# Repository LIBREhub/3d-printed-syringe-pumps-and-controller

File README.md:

# 3D printable syringe pumps and controller  

This project is a free and open-source design of versatile lab equipment - syringe pumps and a dual controller, here detailed for microfluidic droplet generation - a modification from this [Open-Source Syringe Pump design](https://doi.org/10.1134/S1061934820030156).

Find about more about this platform and other open-source hardware for bioimaging on the [LIBRE hub website](https://librehub.github.io/). Follow us! [#twitter](https://twitter.com/WenzelLab) [#YouTube](https://www.youtube.com/@librehub) [#LinkedIn](https://www.linkedin.com/company/92802424) [#instagram](https://www.instagram.com/wenzellab/) [#Printables](https://www.printables.com/@WenzelLab), [IIBM website](https://ingenieriabiologicaymedica.uc.cl/en/people/faculty/821-tobias-wenzel)

## Background

A syringe pump is a device that delivers precise and accurate amounts of fluid over a broad range of flow rates. These devices are versatile and can be used across various fields like healthcare, research, and development, playing a crucial role in scenarios such as controlled drug delivery in hospitals, chemical reaction control in labs, and more.

There are many 3D-printable syringe pump designs available, each with its unique features and capabilities. However, this [Open-Source Syringe Pump design](https://doi.org/10.1134/S1061934820030156) developed by the [Mass Spectrometry Research Group](https://www.mass-spec.ru/projects/diy/syringe_pump/eng/), Analytical Chemistry Division, Chemistry Department of Moscow State University, appealed to our LIBRE Hub team with its design and functionality.

Our goal with this modification and enhancement is to make this open-source syringe pump design more useful to microfluidics and generally more accessible, adaptable, and user-friendly, thus extending its potential use within the broader community.

## Usage

### Instructions
This Repository provides documentation on how to build the pumps and the controller. Just [follow the instructions here](https://wenzel-lab.github.io/syringe-pumps-and-controller/)

This project is documented with GitBuilding - an Open Source project for documenting hardware projects. For more information on the GitBuilding project or how
to install GitBuilding, please see the [GitBuilding website](http://gitbuilding.io)

## Design files and source code

* Hardware design
    * [Link to OnShape CAD files of printable syringe pump parts](https://cad.onshape.com/documents/20c077b452e92115525d4fed/w/71118f46b0924c1bb22b1150/e/9d30ca00efa721d242d78d3f?renderMode=0&uiState=64bd5f2a8bef574246b008b9)
    * [Link to OnShape CAD files of the printable controller enclosure](https://cad.onshape.com/documents/24a5022fafc4edd0c24874dd/w/35c6569cda7c2fa4439727d4/e/9dbcdcaba091e21e6a91c62c?renderMode=0&uiState=64bd5f3f0aa451311c1bb6ad)
* Software source code
    * [Code to upload onto the Raspberry Pi Pico controller](https://github.com/wenzel-lab/syringe-pumps-and-controller/blob/docu-v1/software/firmwareV1.ino)

### How do I edit the documentation?

To edit the documentation, you do not need to install anything, but you will need to
install something to build the final version of the documentation (such as a website).
The documentation files can be opened in a plain text editor such as Windows Notepad,
Notepad++, gedit, VS Code, etc. GitBuilding also comes with a browser-based editor that
displays a live display of the final HTML documentation.

If you have ever used [markdown](https://www.markdownguide.org/basic-syntax/), you will
notice that the files you are editing are markdown files. GitBuilding uses an extended
markdown syntax (that we call BuildUp). This allows you to keep track of parts in the
documentation. More detail on the documentation is available on the
[GitBuilding website](https://gitbuilding.io/syntax/). There is also additional
[syntax for configuration](https://gitbuilding.io/syntax/buildconfsyntax) and for
[part libraries](https://gitbuilding.io/syntax/builduplibrary/).

## Contribute

Enjoy building and using your improved Open-Source Syringe Pump! We look forward to hearing about your experiences and any further improvements you might have. Make a pull request or [open an issue](https://github.com/wenzel-lab/syringe-pumps-and-controller/issues/new).
For interactions in our team and with the community, apply the [GOSH Code of Conduct](https://openhardware.science/gosh-2017/gosh-code-of-conduct/).

## License

[GNU General Public License v3.0](LICENSE) by Tomás Astudillo, Matías Hurtado, Pierre Padilla-Huamantinco, Tobias Wenzel, and the [original design team](https://www.mass-spec.ru/projects/diy/syringe_pump/eng/). This project is Open Source Hardware - please acknowledge us when using the hardware or sharing modifications.

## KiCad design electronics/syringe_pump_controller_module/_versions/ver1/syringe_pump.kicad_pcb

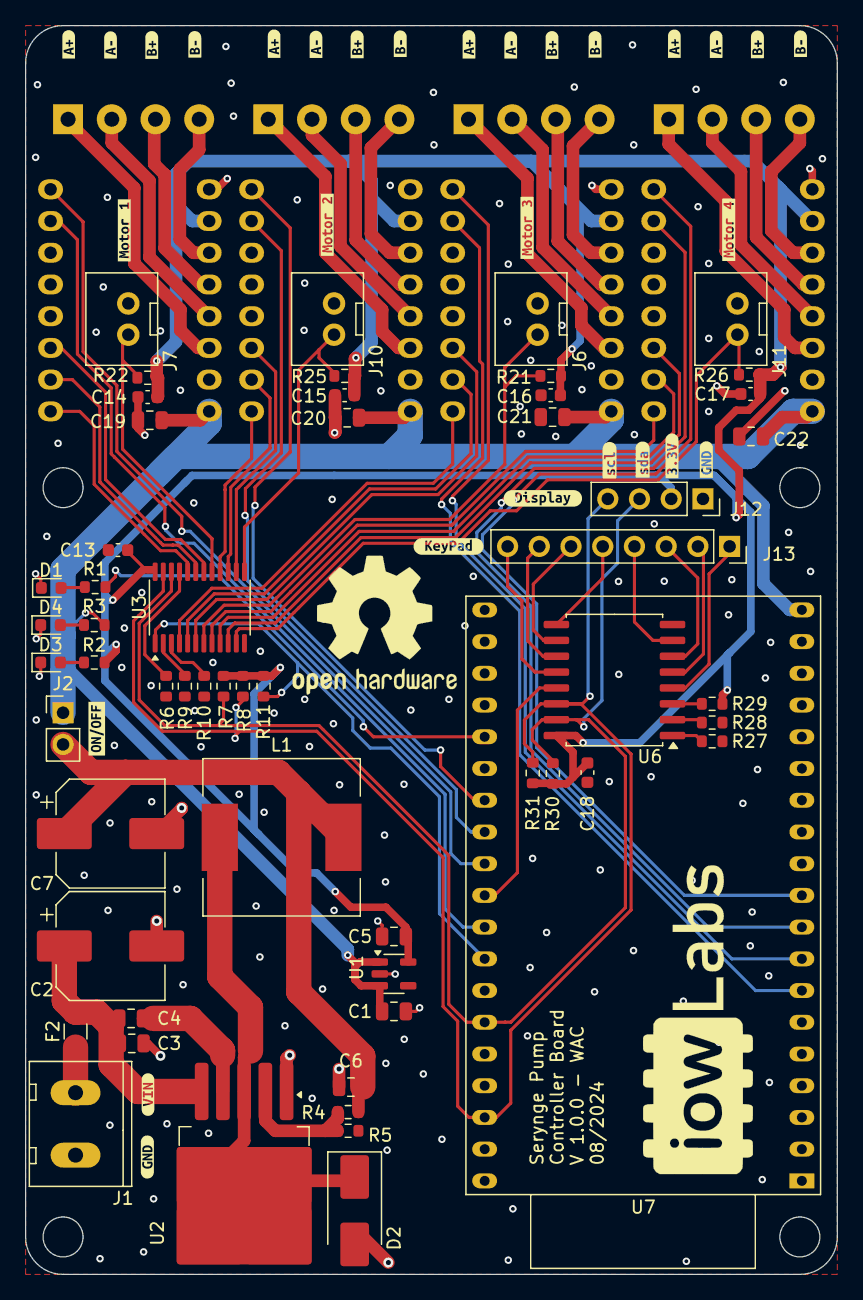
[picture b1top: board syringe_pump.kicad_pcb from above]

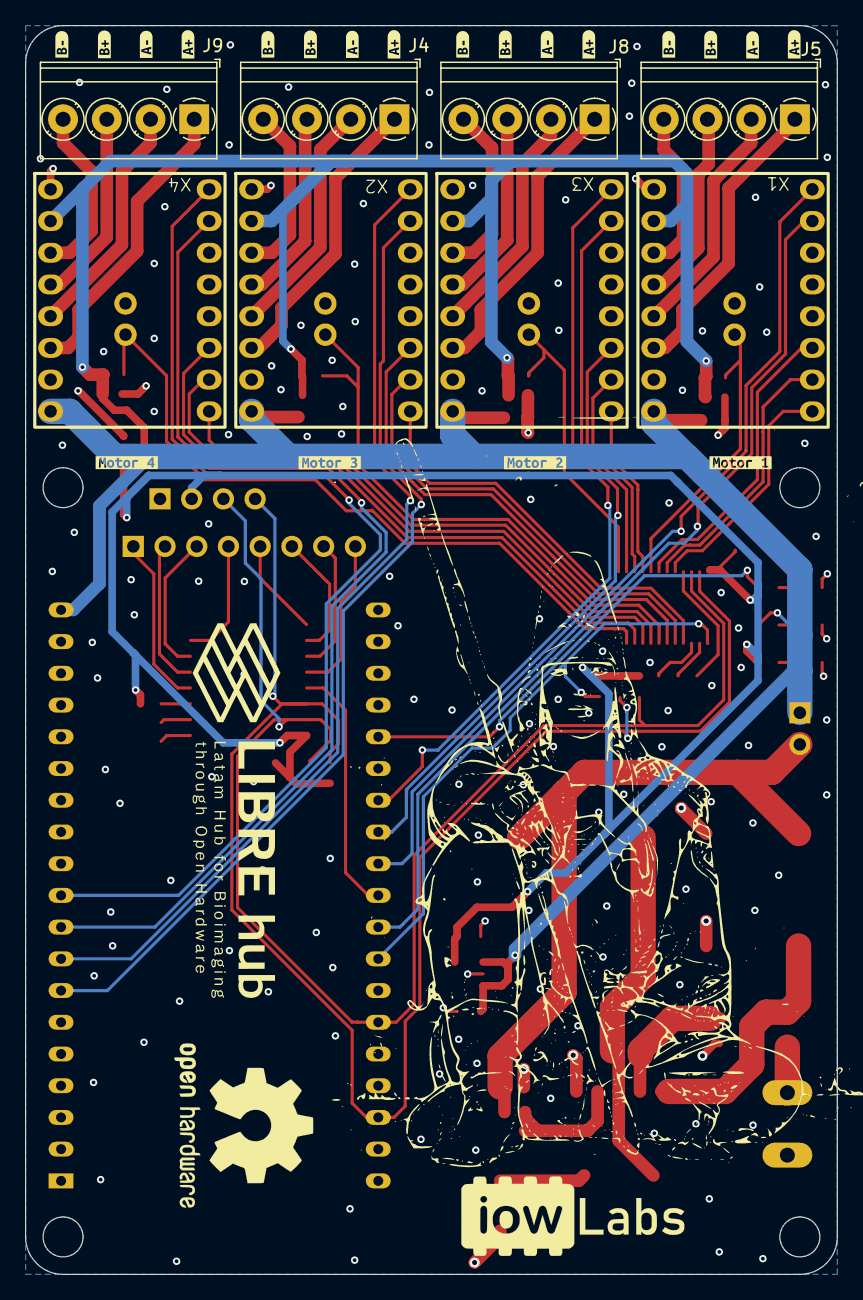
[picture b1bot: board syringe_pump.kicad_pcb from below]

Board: 2 copper layers, 65.0 x 100.0 mm, 113 parts (28 on the bottom side), 71 nets.

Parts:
C1, C3, C4, C5, C6, C19, C20, C21, C22: 1u; C_0805_2012Metric
C2: 220uF; CP_Elec_8x10.5
C7: 330uF; CP_Elec_8x10.5
C13, C14, C15, C16, C17, C18: 100n; C_0603_1608Metric
D1, D3, D4: LED; LED_0603_1608Metric
D2: B540; D_SMB_Handsoldering
F2: FUSE; Fuse_1206_3216Metric
J1: IN; Tb-2x1-5p-TH-V
J2: ON OFF; PinHeader_1x02_P2.54mm_Vertical
J4, J5, J8, J9: HDR-4x1; TerminalBlock_Phoenix_PT-1,5-4-3.5-H_1x04_P3.50mm_Horizontal
J6, J7, J10, J11: EndSwitch; JST-XH-2x1-2.5p-TH-V
J12: Conn_01x04; PinSocket_1x04_P2.54mm_Vertical
J13: Conn_01x08; PinSocket_1x08_P2.54mm_Vertical
L1: 47uH; L_12x12mm_H8mm
R1, R2, R3: 1k; R_0603_1608Metric
R4, R6, R9, R10, R11: 10K; R_0603_1608Metric
R5: 3.3K; R_0603_1608Metric
R7, R8, R21, R22, R25, R26, R27, R28, R29, R30, R31: 10k; R_0603_1608Metric
U1: AP2112K-3.3; SOT-23-5
U2: XL4015; TO-263-5_TabPin3
U3: PCA9555PW; TSSOP-24_4.4x7.8mm_P0.65mm
U6: PCF8574; SOIC-16W_7.5x10.3mm_P1.27mm
U7: ESP32-DevKitC
X1, X2, X3, X4: TCM2209
kibuzzard-66A405FA: G***; kibuzzard-66A405FA
kibuzzard-66A40617: G***; kibuzzard-66A40617
kibuzzard-66C22E4F, kibuzzard-66C22E4F#2, kibuzzard-66C22E4F#3, kibuzzard-66C22E4F#4, kibuzzard-66C22E4F#5, kibuzzard-66C22E4F#6, kibuzzard-66C22E4F#7, kibuzzard-66C22E4F#8: G***; kibuzzard-66C22E4F
kibuzzard-66C22E62, kibuzzard-66C22E62#2, kibuzzard-66C22E62#3, kibuzzard-66C22E62#4, kibuzzard-66C22E62#5, kibuzzard-66C22E62#6, kibuzzard-66C22E62#7, kibuzzard-66C22E62#8: G***; kibuzzard-66C22E62
kibuzzard-66C22E71, kibuzzard-66C22E71#2, kibuzzard-66C22E71#3, kibuzzard-66C22E71#4, kibuzzard-66C22E71#5, kibuzzard-66C22E71#6, kibuzzard-66C22E71#7, kibuzzard-66C22E71#8: G***; kibuzzard-66C22E71
kibuzzard-66C22E91, kibuzzard-66C22E91#2, kibuzzard-66C22E91#3, kibuzzard-66C22E91#4, kibuzzard-66C22E91#5, kibuzzard-66C22E91#6, kibuzzard-66C22E91#7, kibuzzard-66C22E91#8: G***; kibuzzard-66C22E91
kibuzzard-66C26F7C: G***; kibuzzard-66C26F7C
kibuzzard-66C268D3, kibuzzard-66C268D3#2: G***; kibuzzard-66C268D3
kibuzzard-66C268F5, kibuzzard-66C268F5#2: G***; kibuzzard-66C268F5
kibuzzard-66C271FC: G***; kibuzzard-66C271FC
kibuzzard-66C2695E, kibuzzard-66C2695E#2: G***; kibuzzard-66C2695E
kibuzzard-66C26938, kibuzzard-66C26938#2: G***; kibuzzard-66C26938
kibuzzard-66C27154: G***; kibuzzard-66C27154
kibuzzard-66C27168: G***; kibuzzard-66C27168
kibuzzard-66C27204: G***; kibuzzard-66C27204
kibuzzard-66C27224: G***; kibuzzard-66C27224
kibuzzard-66C27242: G***; kibuzzard-66C27242

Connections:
+3V3: C5.1, C13.1, C14.1, C15.1, C16.1, C17.1, C18.1, J12.2, R2.1, R7.1, R8.1, R11.1, R21.1, R22.1, R25.1, R26.1, R29.1, R30.1, R31.1, U1.5 (VOUT), U3.24 (VDD), U6.16 (VDD), X1.10 (VL), X2.10 (VL), X3.10 (VL), X4.10 (VL)
FB: R4.2, R5.1, U2.2 (FB)
GND: C1.2, C2.2, C3.2, C5.2, C6.2, C7.2, C13.2, C14.2, C15.2, C16.2, C17.2, C18.2, C19.2, C20.2, C21.2, C22.2, D1.1 (K), D2.2 (A), D3.1 (K), D4.1 (K), J1.1, J6.2, J7.2, J10.2, J11.2, J12.1, R5.2, R6.2, R9.2, R10.2, R27.1, R28.1, U1.2 (GND), U2.1 (GND), U3.12 (VSS), U6.8 (VSS), U7.14 (GND), U7.32 (GND), U7.38 (GND), X1.9 (GND), X1.15 (GND), X2.9 (GND), X2.15 (GND), X3.9 (GND), X3.15 (GND), X4.9 (GND), X4.15 (GND)
INT_KP: U6.13 (~INT), U7.29 (GPIO5)
INT_MGA: R11.2, U3.1 (~INT), U7.31 (GPIO19)
LED: R1.1, U7.24 (ADC2_CH2/GPIO2)
M1_A1: J5.1, X1.14 (A1)
M1_A2: J5.2, X1.13 (A2)
M1_B1: J5.3, X1.12 (B1)
M1_B2: J5.4, X1.11 (B2)
M1_DIR: U7.28 (GPIO17), X1.8 (DIR)
M1_EN: U3.20 (IO1_7), X1.1 (EN)
M1_ES: J7.1, R22.2, U3.17 (IO1_4)
M1_MS1: U3.19 (IO1_6), X1.2 (MS1)
M1_MS2: U3.18 (IO1_5), X1.3 (MS2)
M1_STEP: U7.30 (GPIO18), X1.7 (STEP)
M2_A1: J8.1, X3.14 (A1)
M2_A2: J8.2, X3.13 (A2)
M2_B1: J8.3, X3.12 (B1)
M2_B2: J8.4, X3.11 (B2)
M2_DIR: U7.26 (ADC2_CH0/GPIO4), X3.8 (DIR)
M2_EN: U3.16 (IO1_3), X3.1 (EN)
M2_ES: J10.1, R25.2, U3.13 (IO1_0)
M2_MS1: U3.15 (IO1_2), X3.2 (MS1)
M2_MS2: U3.14 (IO1_1), X3.3 (MS2)
M2_STEP: U7.27 (GPIO16), X3.7 (STEP)
M3_A1: J4.1, X2.14 (A1)
M3_A2: J4.2, X2.13 (A2)
M3_B1: J4.3, X2.12 (B1)
M3_B2: J4.4, X2.11 (B2)
M3_DIR: U7.8 (32K_XN/GPIO33/ADC1_CH5), X2.8 (DIR)
M3_EN: U3.4 (IO0_0), X2.1 (EN)
M3_ES: J6.1, R21.2, U3.7 (IO0_3)
M3_MS1: U3.5 (IO0_1), X2.2 (MS1)
M3_MS2: U3.6 (IO0_2), X2.3 (MS2)
M3_STEP: U7.7 (32K_XP/GPIO32/ADC1_CH4), X2.7 (STEP)
M4_A1: J9.1, X4.14 (A1)
M4_A2: J9.2, X4.13 (A2)
M4_B1: J9.3, X4.12 (B1)
M4_B2: J9.4, X4.11 (B2)
M4_DIR: U7.10 (DAC_2/ADC2_CH9/GPIO26), X4.8 (DIR)
M4_EN: U3.8 (IO0_4), X4.1 (EN)
M4_ES: J11.1, R26.2, U3.11 (IO0_7)
M4_MS1: U3.9 (IO0_5), X4.2 (MS1)
M4_MS2: U3.10 (IO0_6), X4.3 (MS2)
M4_STEP: U7.9 (DAC_1/ADC2_CH8/GPIO25), X4.7 (STEP)
unnamed: D1.2 (A), R1.2
unnamed: D2.1 (K), L1.1, U2.3 (SW)
unnamed: D3.2 (A), R2.2
unnamed: D4.2 (A), R3.2
unnamed: F2.1, J1.2
unnamed: J13.1, U6.4 (P0)
unnamed: J13.2, U6.5 (P1)
unnamed: J13.3, U6.6 (P2)
unnamed: J13.4, U6.7 (P3)
unnamed: J13.5, U6.9 (P4)
unnamed: J13.6, U6.10 (P5)
unnamed: J13.7, U6.11 (P6)
unnamed: J13.8, U6.12 (P7)
unnamed: C4.2, U2.4 (VC)
unnamed: R6.1, U3.21 (A0)
unnamed: R9.1, U3.2 (A1)
unnamed: R10.1, U3.3 (A2)
unnamed: R27.2, U6.1 (A0)
unnamed: R28.2, U6.2 (A1)
unnamed: R29.2, U6.3 (A2)
SCL: J12.4, R8.2, R31.2, U3.23 (SDA), U6.14 (SCL), U7.36 (GPIO22)
SDA: J12.3, R7.2, R30.2, U3.22 (SCL), U6.15 (SDA), U7.33 (GPIO21)
VIN_5V: C6.1, C7.1, J2.2, L1.2, R4.1
VIN_12V: C2.1, C3.1, C4.1, F2.2, U2.5 (VIN)
VM: C1.1, C19.1, C20.1, C21.1, C22.1, J2.1, R3.1, U1.1 (VIN), U1.3 (EN), U7.19 (5V), X1.16 (VM), X2.16 (VM), X3.16 (VM), X4.16 (VM)

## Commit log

2024-12-06 logo
2025-01-06 v2 of module version. fixing minor bugs and redistribute components on the board
2025-01-06 Deploying to docu-v2 from @ 389b25fcc70ce03c4f44ef68897344b781335110 🚀
2025-01-28 adding gerber files for V2
